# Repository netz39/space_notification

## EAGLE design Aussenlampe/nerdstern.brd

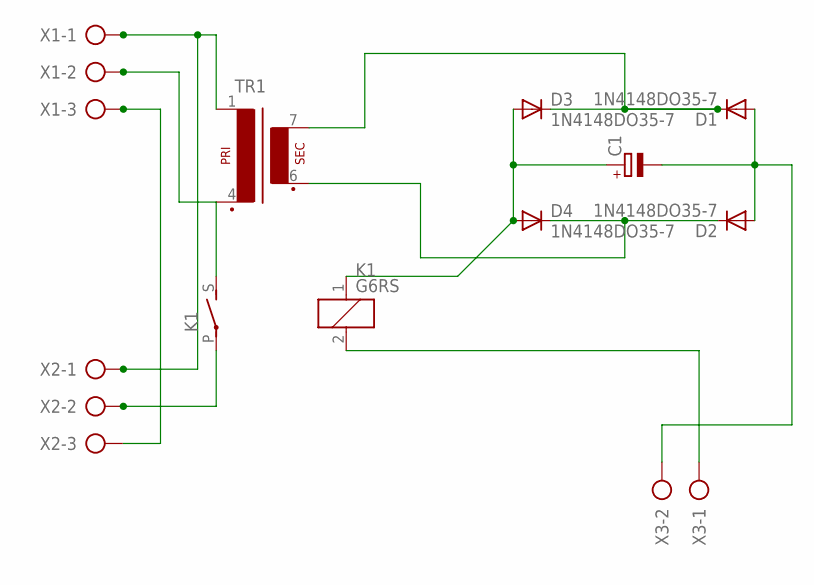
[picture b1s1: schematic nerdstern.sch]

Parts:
C1: CPOL-EUE2-5; E2-5
D1, D2, D3, D4: 1N4148DO35-7; DO35-7
K1: G6RS
TR1: EE20-1
X1, X2: AK500/3
X3: AK500/2

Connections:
GND: K1.2, X3.1
unnamed: K1.S, TR1.4 (P2), X1.2
unnamed: K1.P, X2.2
unnamed: TR1.1, X1.1, X2.1
unnamed: D1.C, D3.C, TR1.7 (S4)
unnamed: C1.+, D3.A, D4.A, K1.1
unnamed: C1.-, D1.A, D2.A, X3.2
unnamed: D2.C, D4.C, TR1.6 (S3)
unnamed: X1.3, X2.3

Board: 2 copper layers, 10 parts (0 on the bottom side), 9 nets, no tracks yet.
